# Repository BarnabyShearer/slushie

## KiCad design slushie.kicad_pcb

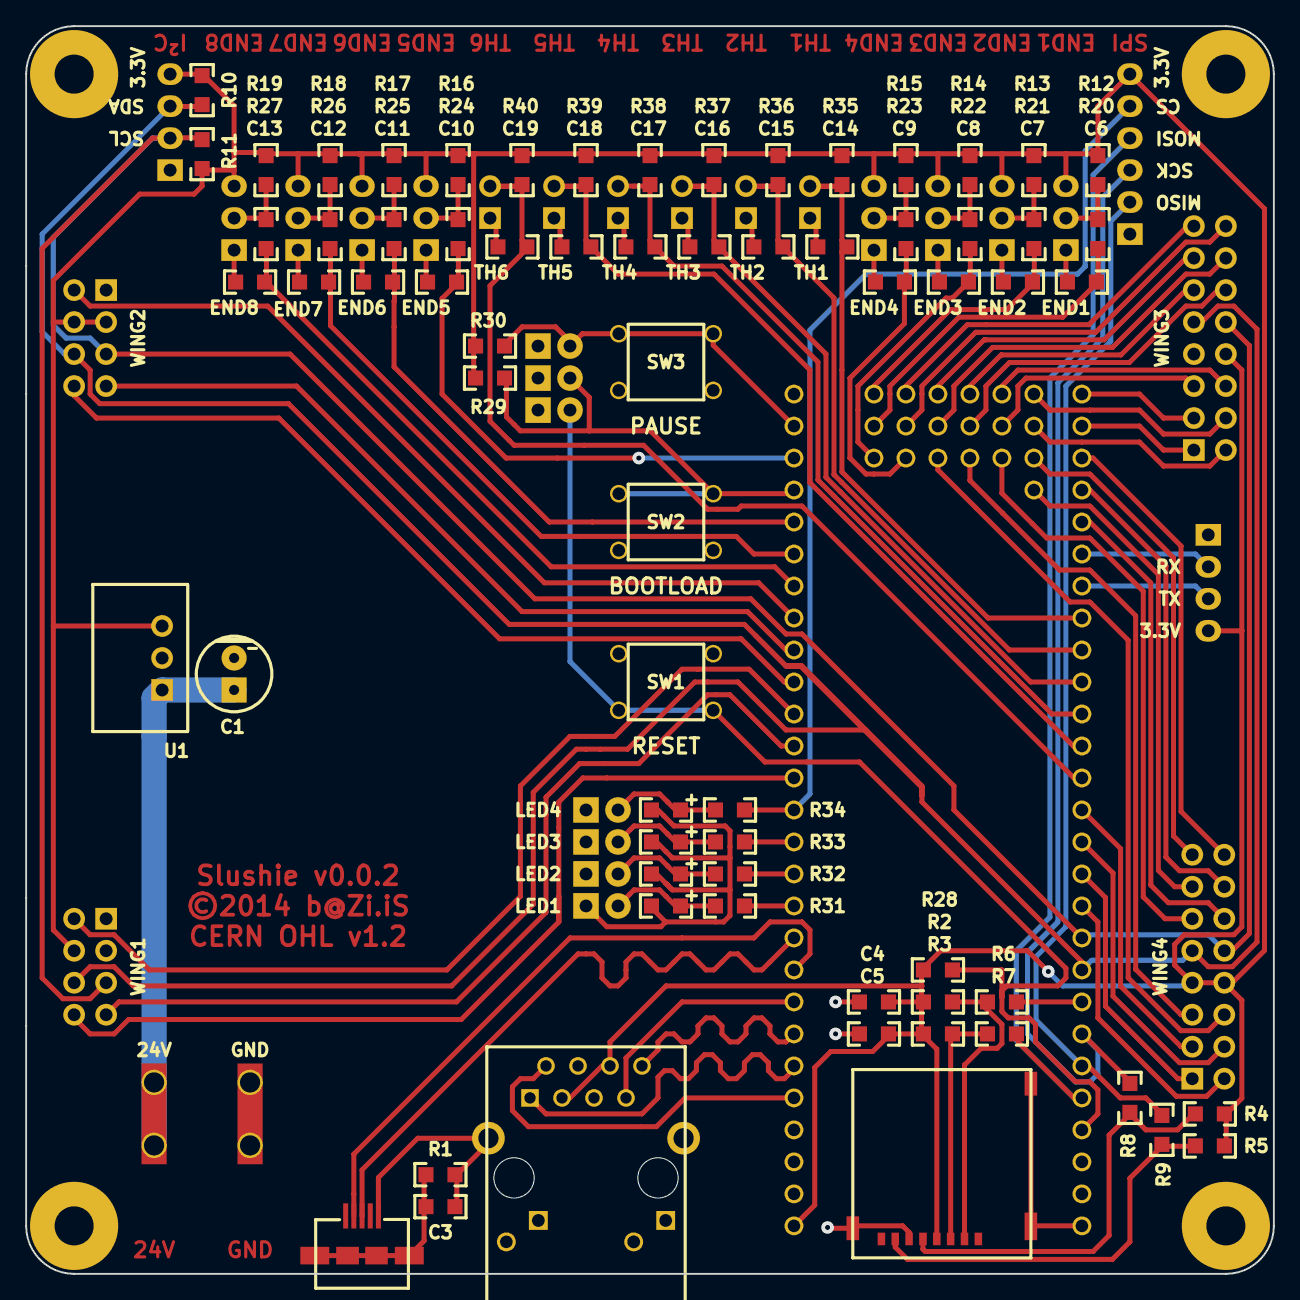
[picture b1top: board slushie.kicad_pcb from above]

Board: 2 copper layers, 99.1 x 99.1 mm, 104 parts (0 on the bottom side), 85 nets.

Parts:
BOOT1: CONN_2; Pin_Header_Straight_1x02
C1: 22µF; Capacitor5x11RM2.5
C3: 4.7nF; 0805C
C4: 1µF; 0805C
C5, C6, C7, C8, C9, C10, C11, C12, C13: 0.1µF; 0805C
C14, C15, C16, C17, C18, C19: 10µF; 0805C
D1, D2, D3, D4: LED; 0805LED
END1, END2, END3, END4, END5, END6, END7, END8: END; Pin_Header_Right_Angle_1x03
ETHERNET1: RJ45-TRANSFO; MJF12T3L-KF06B3YG-0808
I2C1: I²C; Pin_Header_Straight_1x04
LED1, LED2, LED3, LED4: CONN_2; Pin_Header_Straight_1x02
M1, M2, M3, M4: CONN_1; MountingHole_3-1mm
P1, P2: CONN_1; TabRA
PAUSE1: CONN_2; Pin_Header_Straight_1x02
R1: 1M; 0805R
R2, R3, R4, R5, R28, R29, R30: 10k; 0805R
R6, R7, R8, R9: 270; 0805R
R10, R11: 2k2; 0805R
R12, R13, R14, R15, R16, R17, R18, R19, R31, R32, R33, R34: 1k; 0805R
R20, R21, R22, R23, R24, R25, R26, R27: 5k6; 0805R
R35, R36, R37, R38, R39, R40: 4k7; 0805R
RESET1: CONN_2; Pin_Header_Straight_1x02
SD1: MicroSD; MICRO_SD
SPI1: SPI; Pin_Header_Straight_1x06
SW1, SW2, SW3: SPST; Tactswitch
TH1, TH2, TH3, TH4, TH5, TH6: TH; Pin_Header_Angled_2x01
U1: TR05S
U2: LPC1769 LPCXpresso; LPCXPRESSO_LPC1769
UART1: UART; Pin_Header_Straight_1x04
USB1: USB-MINI-B; USB_MICRO_B
WING1, WING2: CONN_4X2; Socket_Strip_Angled_2x04
WING3, WING4: WINGSTEP; Socket_Strip_Angled_2x08

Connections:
+3.3V: C4.1, C5.1, END1.3, END2.3, END3.3, END4.3, END5.3, END6.3, END7.3, END8.3, ETHERNET1.3, ETHERNET1.6, I2C1.4, R2.1, R3.1, R4.1, R5.1, R10.2, R11.2, R12.1, R13.1, R14.1, R15.1, R16.1, R17.1, R18.1, R19.1, R28.1, R29.1, R30.1, R35.1, R36.1, R37.1, R38.1, R39.1, R40.1, SD1.4, SPI1.6, U1.3, U2.28, UART1.4, WING1.4, WING2.3, WING2.4, WING3.8, WING4.7, WING4.8
/BOOT: BOOT1.2, R29.2, SW2.1, U2.51
/D+: U2.37, USB1.3
/D-: U2.36, USB1.2
/DIR0: U2.58, WING3.4
/DIR1: U2.60, WING3.5
/DIR2: U2.67, WING3.13
/DIR3: U2.69, WING3.16
/DIR4: U2.13, WING4.4
/DIR5: U2.62, WING4.5
/DIR6: U2.55, WING4.13
/DIR7: U2.25, WING4.16
/EN0: U2.26, WING3.1
/EN1: U2.61, WING3.6
/EN2: U2.63, WING3.12
/EN3: U2.70, WING3.15
/EN4: U2.12, WING4.1
/EN5: U2.65, WING4.6
/EN6: U2.23, WING4.12
/EN7: U2.56, WING4.15
/END0: C6.1, R20.2, U2.72
/END1: C7.1, R21.2, U2.73
/END2: C8.1, R22.2, U2.71
/END3: C9.1, R23.2, U2.68
/END4: C10.1, R24.2, U2.52
/END5: C11.1, R25.2, U2.50
/END6: C12.1, R26.2, U2.49
/END7: C13.1, R27.2, U2.48
/LED1: R31.1, U2.38
/LED2: R32.1, U2.39
/LED3: R33.1, U2.40
/LED4: R34.1, SPI1.5, U2.41
/MISO: R9.2, SPI1.2, U2.6
/MOSI: R7.2, SPI1.4, U2.5
/PAUSE: PAUSE1.2, R30.2, SW3.1, U2.53
/PWM0: U2.44, WING1.2
/PWM1: U2.43, WING1.7
/PWM2: U2.42, WING1.8
/PWM3: U2.47, WING2.2
/PWM4: U2.46, WING2.7
/PWM5: U2.45, WING2.8
/RD+: ETHERNET1.1, U2.33
/RD-: ETHERNET1.2, U2.32
/RESET: R28.2, RESET1.2, SW1.1, U2.4
/RX: U2.22, UART1.2
/SCK: R8.2, SPI1.3, U2.7
/SCL: I2C1.2, R11.1, U2.10, WING1.5, WING2.5, WING3.10, WING4.10
/SD: R6.2, U2.8
/SDA: I2C1.3, R10.1, U2.9, WING1.6, WING2.6, WING3.9, WING4.9
/STP0: U2.57, WING3.2
/STP1: U2.27, WING3.3
/STP2: U2.64, WING3.11
/STP3: U2.66, WING3.14
/STP4: U2.11, WING4.2
/STP5: U2.14, WING4.3
/STP6: U2.59, WING4.11
/STP7: U2.24, WING4.14
/TD+: ETHERNET1.7, U2.35
/TD-: ETHERNET1.8, U2.34
/TH0: C14.1, R35.2, TH1.2, U2.20
/TH1: C15.1, R36.2, TH2.2, U2.19
/TH2: C16.1, R37.2, TH3.2, U2.18
/TH3: C17.1, R38.2, TH4.2, U2.17
/TH4: C18.1, R39.2, TH5.2, U2.16
/TH5: C19.1, R40.2, TH6.2, U2.15
/TX: U2.21, UART1.3
GND: BOOT1.1, C1.2, C3.2, C4.2, C5.2, C6.2, C7.2, C8.2, C9.2, C10.2, C11.2, C12.2, C13.2, C14.2, C15.2, C16.2, C17.2, C18.2, C19.2, D1.2, D2.2, D3.2, D4.2, END1.1, END2.1, END3.1, END4.1, END5.1, END6.1, END7.1, END8.1, ETHERNET1.4, ETHERNET1.5, ETHERNET1.13, I2C1.1, LED1.1, LED2.1, LED3.1, LED4.1, M1.1, M2.1, M3.1, M4.1, P2.1, PAUSE1.1, R1.2, RESET1.1, SD1.6, SD1.SHLD, SPI1.1, SW1.2, SW2.2, SW3.2, TH1.1, TH2.1, TH3.1, TH4.1, TH5.1, TH6.1, U1.2, U2.1, U2.54, UART1.1, USB1.5, WING1.3, WING3.7
unnamed: C1.1, P1.1, U1.1
unnamed: C3.1, R1.1, USB1.6, USB1.7, USB1.8, USB1.9
unnamed: D1.1, LED1.2, R31.2
unnamed: D2.1, LED2.2, R32.2
unnamed: D3.1, LED3.2, R33.2
unnamed: D4.1, LED4.2, R34.2
unnamed: END1.2, R12.2, R20.1
unnamed: END2.2, R13.2, R21.1
unnamed: END3.2, R14.2, R22.1
unnamed: END4.2, R15.2, R23.1
unnamed: END5.2, R16.2, R24.1
unnamed: END6.2, R17.2, R25.1
unnamed: END7.2, R18.2, R26.1
unnamed: END8.2, R19.2, R27.1
unnamed: R2.2, R6.1, SD1.2
unnamed: R3.2, R7.1, SD1.3
unnamed: R4.2, R8.1, SD1.5
unnamed: R5.2, R9.1, SD1.7

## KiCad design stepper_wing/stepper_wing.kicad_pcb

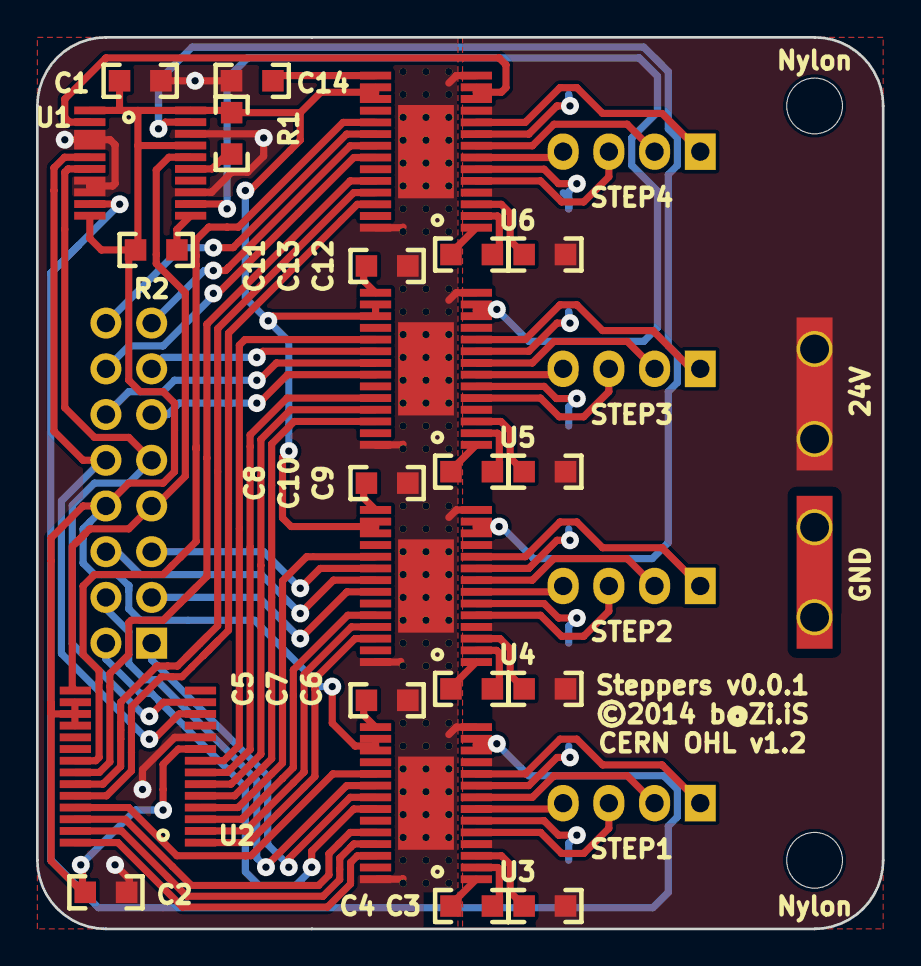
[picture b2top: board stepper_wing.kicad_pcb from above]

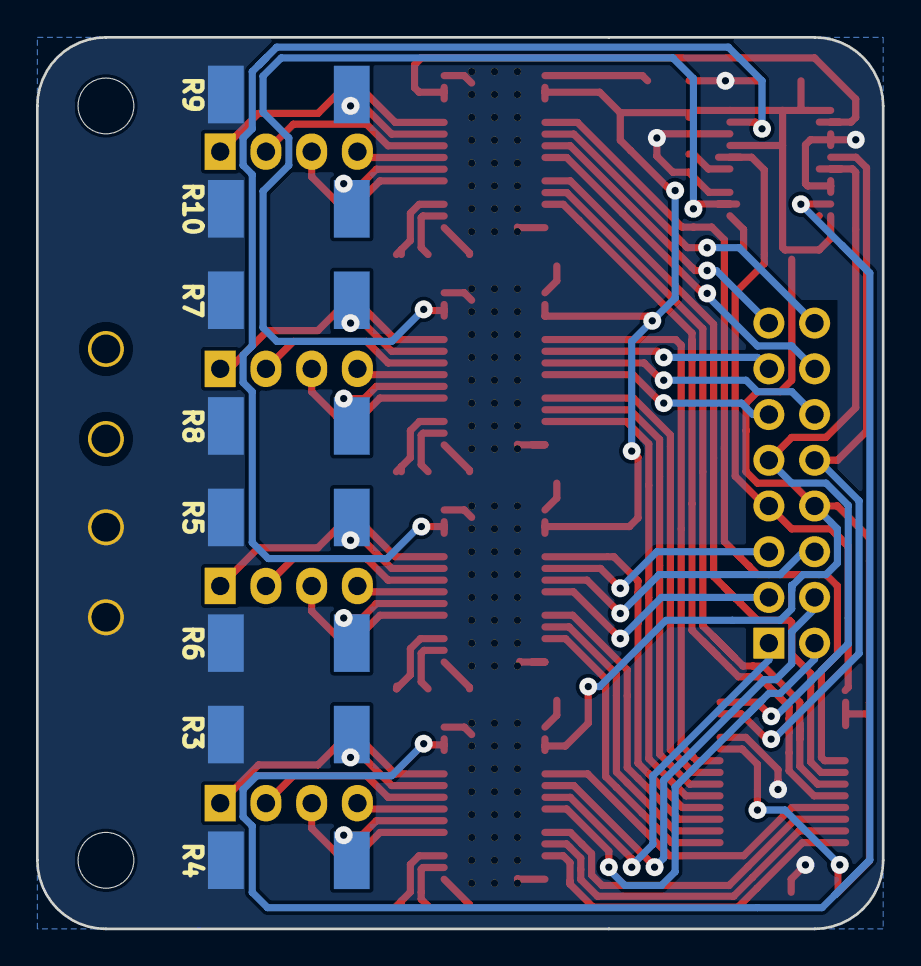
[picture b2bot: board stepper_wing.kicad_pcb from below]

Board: 2 copper layers, 47.0 x 49.5 mm, 39 parts (8 on the bottom side), 80 nets.

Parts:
C1, C2: 1µF; 0805C
C3, C6, C9, C12: 0.1µF; 0805C
C4, C7, C10, C13: 0.01µF; 0805C
C5, C8, C11, C14: 0.47µF; 0805C
M1, M2: Nylon; MountingHole_3-1mm
P1: 24V; TabRA
P2: GND; TabRA
R1: 100k; 0805R
R2: 33k; 0805R
R3, R4, R5, R6, R7, R8, R9, R10: 0.5; R_2512
STEP1, STEP2, STEP3, STEP4: STEP; Pin_Header_Straight_1x04
U1: MCP44X1; TSSOP-20
U2: MCP23017; SSOP-28
U3, U4, U5, U6: DRV8825; TSSOP-28
WING1: WINGSTEP; Pin_Header_Angled_2x08

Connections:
+3.3V: C1.1, C2.1, R1.1, R2.1, U1.1, U1.10, U1.17, U1.20, U2.9, U2.16, U2.17, U2.18, U3.16, U3.17, U4.16, U4.17, U5.16, U5.17, U6.16, U6.17, WING1.8
+24V: C3.1, C6.1, C9.1, C12.1, P1.1, U3.4, U3.11, U4.4, U4.11, U5.4, U5.11, U6.4, U6.11
/ADD: U1.16, U2.15, WING1.7
/SCL: U1.5, U2.12, WING1.10
/SDA: U1.6, U2.13, WING1.9
/Stepper0/DECAY: U2.25, U3.19
/Stepper0/DIR: U3.20, WING1.4
/Stepper0/EN: U3.21, WING1.1
/Stepper0/MODE0: U2.26, U3.24
/Stepper0/MODE1: U2.27, U3.25
/Stepper0/MODE2: U2.28, U3.26
/Stepper0/PW: U1.9, U3.12, U3.13
/Stepper0/STEP: U3.22, WING1.2
/Stepper1/DECAY: U2.4, U4.19
/Stepper1/DIR: U4.20, WING1.5
/Stepper1/EN: U4.21, WING1.6
/Stepper1/MODE0: U2.3, U4.24
/Stepper1/MODE1: U2.2, U4.25
/Stepper1/MODE2: U2.1, U4.26
/Stepper1/PW: U1.19, U4.12, U4.13
/Stepper1/STEP: U4.22, WING1.3
/Stepper2/DECAY: U2.8, U5.19
/Stepper2/DIR: U5.20, WING1.13
/Stepper2/EN: U5.21, WING1.12
/Stepper2/MODE0: U2.7, U5.24
/Stepper2/MODE1: U2.6, U5.25
/Stepper2/MODE2: U2.5, U5.26
/Stepper2/PW: U1.12, U5.12, U5.13
/Stepper2/STEP: U5.22, WING1.11
/Stepper3/DECAY: U2.21, U6.19
/Stepper3/DIR: U6.20, WING1.16
/Stepper3/EN: U6.21, WING1.15
/Stepper3/MODE0: U2.22, U6.24
/Stepper3/MODE1: U2.23, U6.25
/Stepper3/MODE2: U2.24, U6.26
/Stepper3/PW: U1.2, U6.12, U6.13
/Stepper3/STEP: U6.22, WING1.14
GND: C1.2, C2.2, C5.2, C8.2, C11.2, C14.2, P2.1, R3.2, R4.2, R5.2, R6.2, R7.2, R8.2, R9.2, R10.2, U1.3, U1.4, U1.7, U1.8, U1.13, U1.18, U2.10, U3.14, U3.28, U4.14, U4.28, U5.14, U5.28, U6.14, U6.28
unnamed: C3.2, U3.3
unnamed: C4.1, U3.2
unnamed: C4.2, U3.1
unnamed: C5.1, U3.15
unnamed: C6.2, U4.3
unnamed: C7.1, U4.2
unnamed: C7.2, U4.1
unnamed: C8.1, U4.15
unnamed: C9.2, U5.3
unnamed: C10.1, U5.2
unnamed: C10.2, U5.1
unnamed: C11.1, U5.15
unnamed: C12.2, U6.3
unnamed: C13.1, U6.2
unnamed: C13.2, U6.1
unnamed: C14.1, U6.15
unnamed: R1.2, U1.15
unnamed: R2.2, U1.11
unnamed: R3.1, U3.9
unnamed: R4.1, U3.6
unnamed: R5.1, U4.9
unnamed: R6.1, U4.6
unnamed: R7.1, U5.9
unnamed: R8.1, U5.6
unnamed: R9.1, U6.9
unnamed: R10.1, U6.6
unnamed: STEP1.1, U3.10
unnamed: STEP1.2, U3.8
unnamed: STEP1.3, U3.5
unnamed: STEP1.4, U3.7
unnamed: STEP2.1, U4.10
unnamed: STEP2.2, U4.8
unnamed: STEP2.3, U4.5
unnamed: STEP2.4, U4.7
unnamed: STEP3.1, U5.10
unnamed: STEP3.2, U5.8
unnamed: STEP3.3, U5.5
unnamed: STEP3.4, U5.7
unnamed: STEP4.1, U6.10
unnamed: STEP4.2, U6.8
unnamed: STEP4.3, U6.5
unnamed: STEP4.4, U6.7

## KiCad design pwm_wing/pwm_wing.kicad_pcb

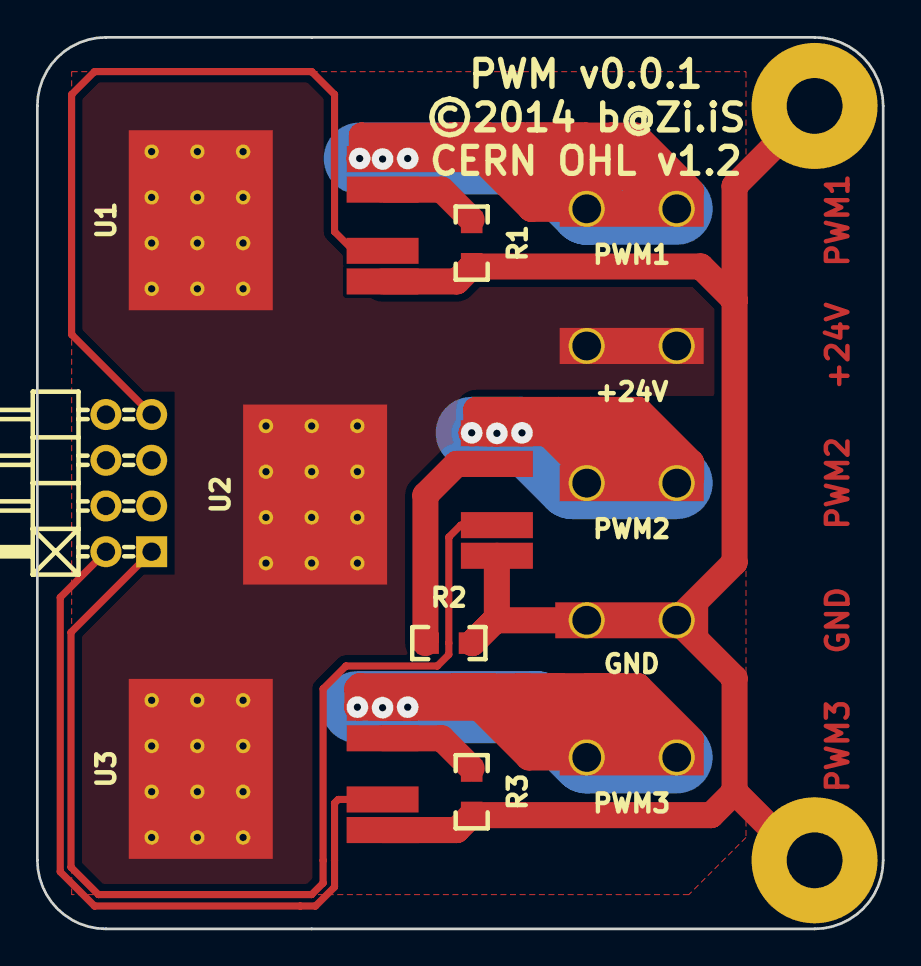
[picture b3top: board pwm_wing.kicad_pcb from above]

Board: 2 copper layers, 47.0 x 49.5 mm, 14 parts (0 on the bottom side), 11 nets.

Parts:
M1, M2: GND; MountingHole_3-1mm
P1: +24V; TabRA
P2: GND; TabRA
P3: CONN_4X2; Pin_Header_Angled_2x04
P4: PWM1; TabRA
P5: PWM2; TabRA
P6: PWM3; TabRA
R1, R2, R3: 1k; 0805R
U1, U2, U3: VN9205-e; P²PAK

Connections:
+24V: P1.1, U1.3, U2.3, U3.3
/PWM0: P3.7, U1.2
/PWM1: P3.1, U2.2
/PWM2: P3.2, U3.2
GND: M1.1, M2.1, P2.1, R1.2, R2.2, R3.2, U1.1, U2.1, U3.1
unnamed: P4.1, U1.5
unnamed: P5.1, U2.5
unnamed: P6.1, U3.5
unnamed: R1.1, U1.4
unnamed: R2.1, U2.4
unnamed: R3.1, U3.4

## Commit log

2014-08-10 init
2014-08-13 ideas
2014-08-16 step wing looking good
2014-08-16 just the spi
2014-08-18 mainboard
2014-08-22 first layout
2014-08-26 clean
2014-08-27 try alt layout
2014-08-31 need to enbigen silk
2014-09-03 tidy
2014-09-14 more titdy
2015-03-18 fixes
2015-06-23 Remove absolute paths
2015-06-23 silly absolute paths where back

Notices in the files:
pwm_wing/pwm_wing.kicad_pcb:
©2014 b@Zi.iS
CERN OHL v1.2
